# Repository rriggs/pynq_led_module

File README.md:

# Modules for Pynq-Z2

This repo contains modules for the TUL Pynq-Z2 board.

This repo was created for a single board, but morphed into a container
for multiple boards as the need for boards grew.

The boards in this repo are:

 1. A [14-segment LED module for the Raspberry Pi header](14-segment_led_module/README.md)
 1. A [7-segment LED module for the Raspberry Pi header](7-segment_led_module/README.md)
 1. A [8-segment LED bar graph module PMOD](bar-graph_led_pmod/README.md)
 1. A [8P DIP switch PMOD](dip_switch_pmod/README.md)
 
This repo contains KiCAD files and Gerbers for those wanting to make their
own boards.  These boards were all auto-routed using FreeRouting.

This project is OSHW (Open Source Hardware), released under the GPLv3 license.

If you are interested in purchasing kits or complete modules, please contant
me at rob@mobilinkd.com.

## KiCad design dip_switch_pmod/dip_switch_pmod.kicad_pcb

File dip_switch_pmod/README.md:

# 8P DIP Switch PMOD

This is a 8-position DIP swith PMOD.  The 9-pin SIP module is for an optional
pull-down resistor array.  It is not strictly necessary as the pins on the
FPGA should have weak pull-downs that can be enabled.

This board expects that there are inline current limiting resistors on the
PMOD signal lines to avoid exceeding the current rating of both the switch
and the FPGA should the FPGA pins be accidentally configured for output
rather than input.

This repo contains KiCAD files and Gerbers for those wanting to make their
own boards.  The board was auto-routed using FreeRouting.

This project is OSHW (Open Source Hardware), released under the GPLv3 license.

If you are interested in purchasing kits or complete modules, please contant
me at rob@mobilinkd.com.

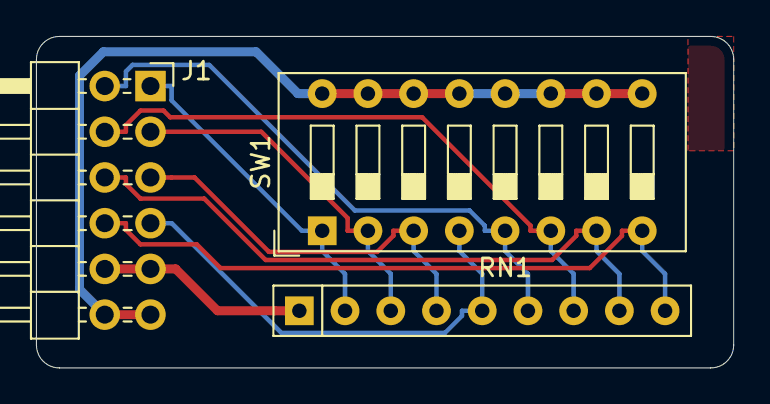
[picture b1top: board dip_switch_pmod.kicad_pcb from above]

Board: 2 copper layers, 38.7 x 18.4 mm, 3 parts (0 on the bottom side), 10 nets.

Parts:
J1: Conn_02x06_Top_Bottom; PinHeader_2x06_P2.54mm_Horizontal
RN1: R_Network08; R_Array_SIP9
SW1: SW_DIP_x08; SW_DIP_SPSTx08_Slide_9.78x22.5mm_W7.62mm_P2.54mm

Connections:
+3V3: J1.6, J1.12, SW1.9, SW1.10, SW1.11, SW1.12, SW1.13, SW1.14, SW1.15, SW1.16
GND: J1.5, J1.11, RN1.1
unnamed: J1.1, RN1.2, SW1.1
unnamed: J1.2, RN1.3, SW1.2
unnamed: J1.3, RN1.4, SW1.3
unnamed: J1.4, RN1.5, SW1.4
unnamed: J1.7, RN1.6, SW1.5
unnamed: J1.8, RN1.7, SW1.6
unnamed: J1.9, RN1.8, SW1.7
unnamed: J1.10, RN1.9, SW1.8

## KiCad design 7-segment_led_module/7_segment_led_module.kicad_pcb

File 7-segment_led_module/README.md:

# 7-Segment LED Module for Pynq-Z2 RPi Header 

This is an add-on board designed for the Pynq-Z2 FPGA development board.
This is a 4-digit LED display using a single LDS-5461BK 7-segment display
module. This board avoids using the pins on the Pynq-Z2 RPi connector
which are shared with the PMOD A connector so that both can be used at the
same time.

This repo contains KiCAD files and Gerbers for those wanting to make their
own boards.  The board was auto-routed using FreeRouting.

This project is OSHW (Open Source Hardware), released under the GPLv3 license.

If you are interested in purchasing kits or complete modules, please contant
me at rob@mobilinkd.com.

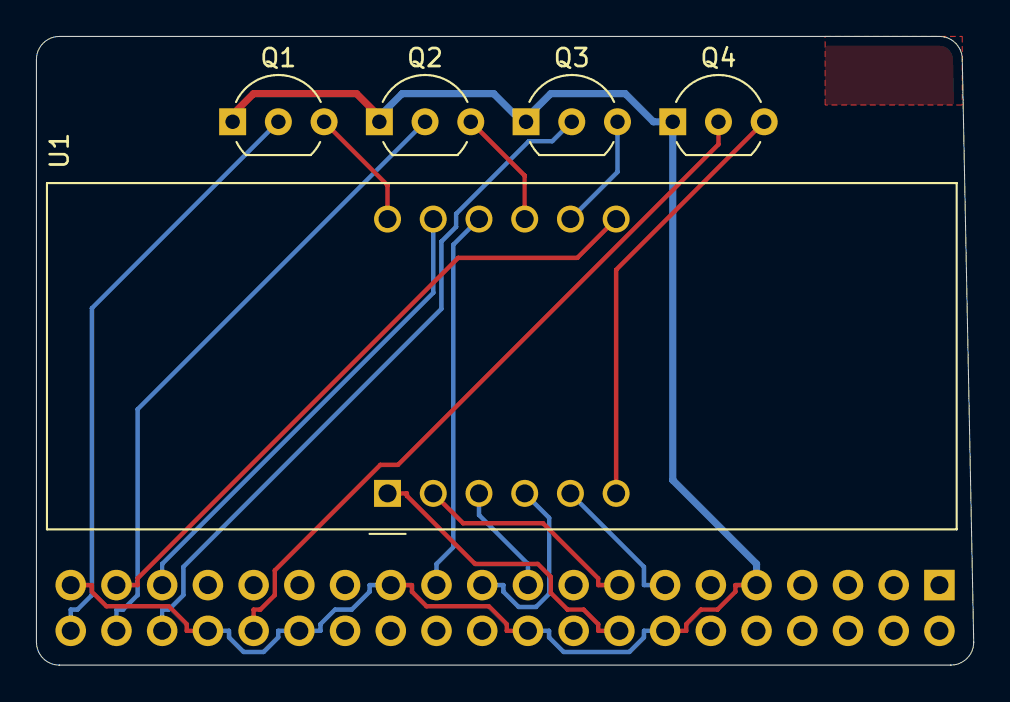
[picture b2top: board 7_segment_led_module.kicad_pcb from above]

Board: 2 copper layers, 52.1 x 34.9 mm, 6 parts (1 on the bottom side), 17 nets.

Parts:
J1: Conn_02x20_Odd_Even; PinSocket_2x20_P2.54mm_Vertical
Q1, Q2, Q3, Q4: 2N7000; TO-92_Inline_Wide
U1: CC56-12CGKWA; CA56-12CGKWA

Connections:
GND: J1.9, J1.14, J1.20, J1.25, J1.30, J1.34, J1.39, Q1.1, Q2.1, Q3.1, Q4.1
unnamed: J1.13, U1.5
unnamed: J1.15, U1.2
unnamed: J1.16, U1.1
unnamed: J1.19, U1.3
unnamed: J1.21, U1.4
unnamed: J1.23, U1.10
unnamed: J1.32, Q4.2
unnamed: J1.35, U1.11
unnamed: J1.36, Q3.2
unnamed: J1.37, U1.7
unnamed: J1.38, Q2.2
unnamed: J1.40, Q1.2
unnamed: Q1.3, U1.12
unnamed: Q2.3, U1.9
unnamed: Q3.3, U1.8
unnamed: Q4.3, U1.6

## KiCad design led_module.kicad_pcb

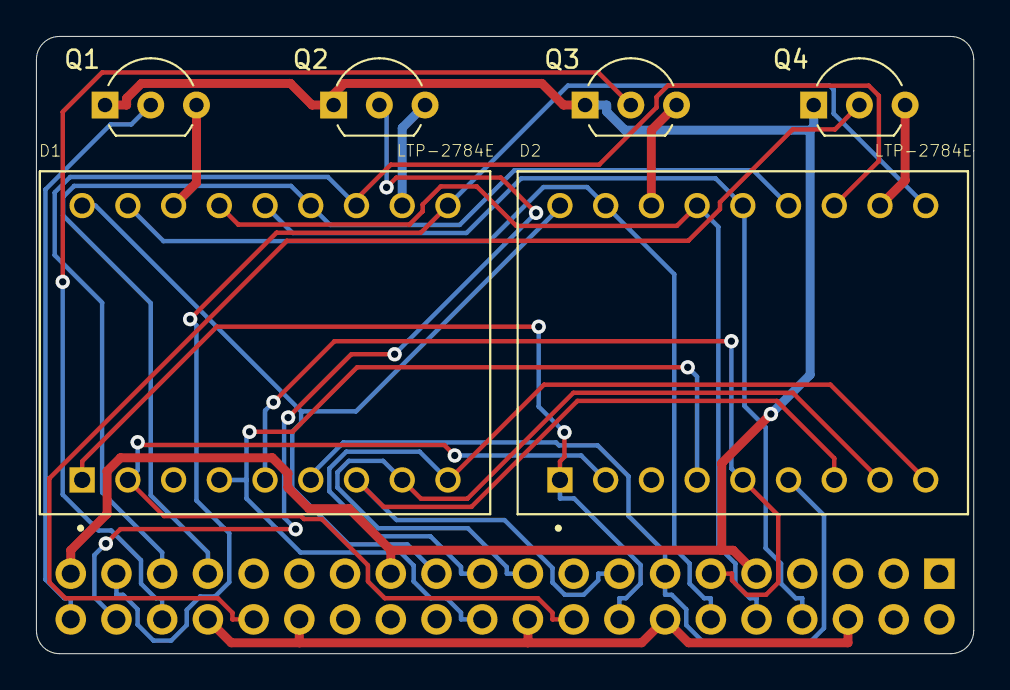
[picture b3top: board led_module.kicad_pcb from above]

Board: 2 copper layers, 52.1 x 34.3 mm, 7 parts (1 on the bottom side), 24 nets.

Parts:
D1, D2: LTP-2784E; DIP1524W51P254L2503H810Q18
J1: Conn_02x20_Odd_Even; PinSocket_2x20_P2.54mm_Vertical
Q1, Q2, Q3, Q4: 2N7000; TO-92L_Inline_Wide

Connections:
GND: J1.6, J1.9, J1.14, J1.20, J1.25, J1.30, J1.34, J1.39, Q1.1, Q2.1, Q3.1, Q4.1
unnamed: D1.1, D2.1, J1.16
unnamed: D1.2, D2.2, J1.18
unnamed: D1.4, D2.4, J1.22
unnamed: D1.5, D2.5, J1.11
unnamed: D1.6, D2.6, J1.13
unnamed: D1.7, D2.7, J1.15
unnamed: D1.8, D2.8, J1.19
unnamed: D1.9, D2.9, J1.21
unnamed: D1.10, D2.10, J1.37
unnamed: D1.11, Q2.3
unnamed: D1.12, D2.12, J1.35
unnamed: D1.13, D2.13, J1.33
unnamed: D1.14, D2.14, J1.8
unnamed: D1.15, D2.15, J1.10
unnamed: D1.16, Q1.3
unnamed: D1.17, D2.17, J1.12
unnamed: D1.18, D2.18, J1.23
unnamed: D2.11, Q4.3
unnamed: D2.16, Q3.3
unnamed: J1.32, Q4.2
unnamed: J1.36, Q3.2
unnamed: J1.38, Q2.2
unnamed: J1.40, Q1.2

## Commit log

2019-10-13 Initial LED module design.
2019-10-13 Rev B. Improve brightness by using 2N7000 MOSFETs to switch digits. Use only RPi pins that are not shared with PMOD-A.
2019-10-13 Add README.md file to project.
2019-10-13 Add board rendering to README.md.
2019-10-13 Add/use 14-segment 3D model for module rendering.
2019-10-13 Update README.md.
2019-10-25 Update to rev C. Pin 1 was connected to ground (based on user manual). It is actually connected to 3V3 and is not connected in rev C. Change the footprint for Q1-Q4 to 2.54mm pin spacing to make hand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
2019-10-25 Add XDC for LED module.
2019-12-08 Small update to 14-segment display board.
2019-12-08 Update gitignore.
2019-12-08 Move 14-segment LED module to subdirectory.
2019-12-08 Add new modules: 7-segment dispay, 8P dip switch PMOD, 8P LED bar graph PMOD.
2019-12-08 Update README files.
2019-12-08 Add image for dip switch PMOD.
2019-12-08 Update bar graph README.
2019-12-08 Fix typo in dip switch README.
2019-12-08 Update DIP switch module discription.
